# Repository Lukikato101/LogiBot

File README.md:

# LogiBot

**Low-cost Autonomous Mobile Robot (AMR) for Warehouse Automation**

LogiBot is an autonomous mobile robot project focused on building an affordable and practical warehouse automation platform for small and medium-sized warehouses.

The goal of this project is to develop a reliable AMR system that can transport materials, navigate autonomously, and serve as a foundation for future warehouse automation solutions.

---

## Vision

Warehouse automation should not be limited to large enterprises.

LogiBot aims to make autonomous material transport more accessible by developing a cost-effective AMR platform that can be deployed in real-world warehouse environments.

---

## Project Goals

* Build a reliable autonomous mobile robot platform
* Develop a low-cost warehouse transportation solution
* Create a modular hardware and software architecture
* Support ROS 2 based development
* Enable fleet management and multi-robot operations
* Provide a foundation for future commercial deployment

---

## Current Development Status

### Phase 1 — Mobile Robot Platform

* [ ] Differential drive platform
* [ ] STM32 motor controller
* [ ] Encoder integration
* [ ] IMU integration
* [ ] Battery management

### Phase 2 — ROS 2 Integration

* [ ] ROS 2 communication
* [ ] Robot description (URDF)
* [ ] Teleoperation
* [ ] Odometry

### Phase 3 — Autonomous Navigation

* [ ] Localization
* [ ] Waypoint navigation
* [ ] AprilTag navigation
* [ ] Obstacle detection

### Phase 4 — Warehouse Features

* [ ] Material transport workflow
* [ ] Automatic docking
* [ ] Charging station
* [ ] Fleet management dashboard

### Phase 5 — Field Testing

* [ ] Real warehouse deployment
* [ ] Performance optimization
* [ ] Reliability testing

---

## System Architecture

```text
+------------------------+
|      Fleet Manager     |
+-----------+------------+
            |
            v
+------------------------+
|    ROS 2 Computer      |
| (Raspberry Pi / SBC)   |
+-----------+------------+
            |
            v
+------------------------+
|         STM32          |
|  Motor & Sensor Layer  |
+-----------+------------+
            |
            v
+------------------------+
| Motors / Encoders /    |
| IMU / Safety Sensors   |
+------------------------+
```

---

## Repository Structure

```text
LogiBot/

├── docs/
├── hardware/
├── firmware/
├── software/
├── simulation/
├── dashboard/
├── test/
└── README.md
```

### docs/

Project documentation, architecture, roadmap, and technical notes.

### hardware/

Mechanical design, CAD files, PCB designs, and manufacturing resources.

### firmware/

STM32 firmware for motor control, sensors, and communication.

### software/

ROS 2 packages, navigation stack, robot interfaces, and system integration.

### simulation/

Simulation environments and testing tools.

### dashboard/

Fleet monitoring and management interface.

---

## Technology Stack

### Hardware

* STM32
* Differential Drive Platform
* BLDC/DC Motors
* Encoders
* IMU
* Camera
* Battery Management System

### Software

* ROS 2
* Ubuntu
* C++
* Python
* Micro-ROS
* Gazebo

---

## Contribution Areas

There are many ways to contribute:

### Embedded Systems

* STM32 firmware
* Motor control
* Sensor integration
* Communication protocols

### Robotics Software

* ROS 2 packages
* Navigation
* Localization
* Path planning

### Mechanical Design

* Chassis design
* CAD modeling
* Manufacturing optimization

### Electronics

* PCB design
* Power systems
* Safety circuits

### Simulation

* Gazebo environments
* Testing scenarios
* Validation tools

### Documentation

* Tutorials
* Setup guides
* Technical documentation

---

## How to Contribute

1. Fork the repository
2. Create a feature branch
3. Implement your changes
4. Test your work
5. Submit a Pull Request

Please keep contributions focused, documented, and aligned with the project roadmap.

---

## Roadmap

### V0.1

Basic differential drive robot

### V0.2

ROS 2 integration

### V0.3

Autonomous waypoint navigation

### V0.4

Automatic docking

### V0.5

Fleet management

### V1.0

Warehouse-ready AMR platform

---

## Long-Term Objective

Build an affordable warehouse AMR platform that helps small and medium-sized businesses adopt automation without the high costs typically associated with industrial robotics.

---

## Join the Project

If you are interested in robotics, embedded systems, ROS 2, mechanical design, electronics, or warehouse automation, contributions are welcome.

Together we can build a practical and accessible AMR platform from the ground up.

---

**Project Name:** LogiBot

**Status:** Early Development

**License:** To be determined

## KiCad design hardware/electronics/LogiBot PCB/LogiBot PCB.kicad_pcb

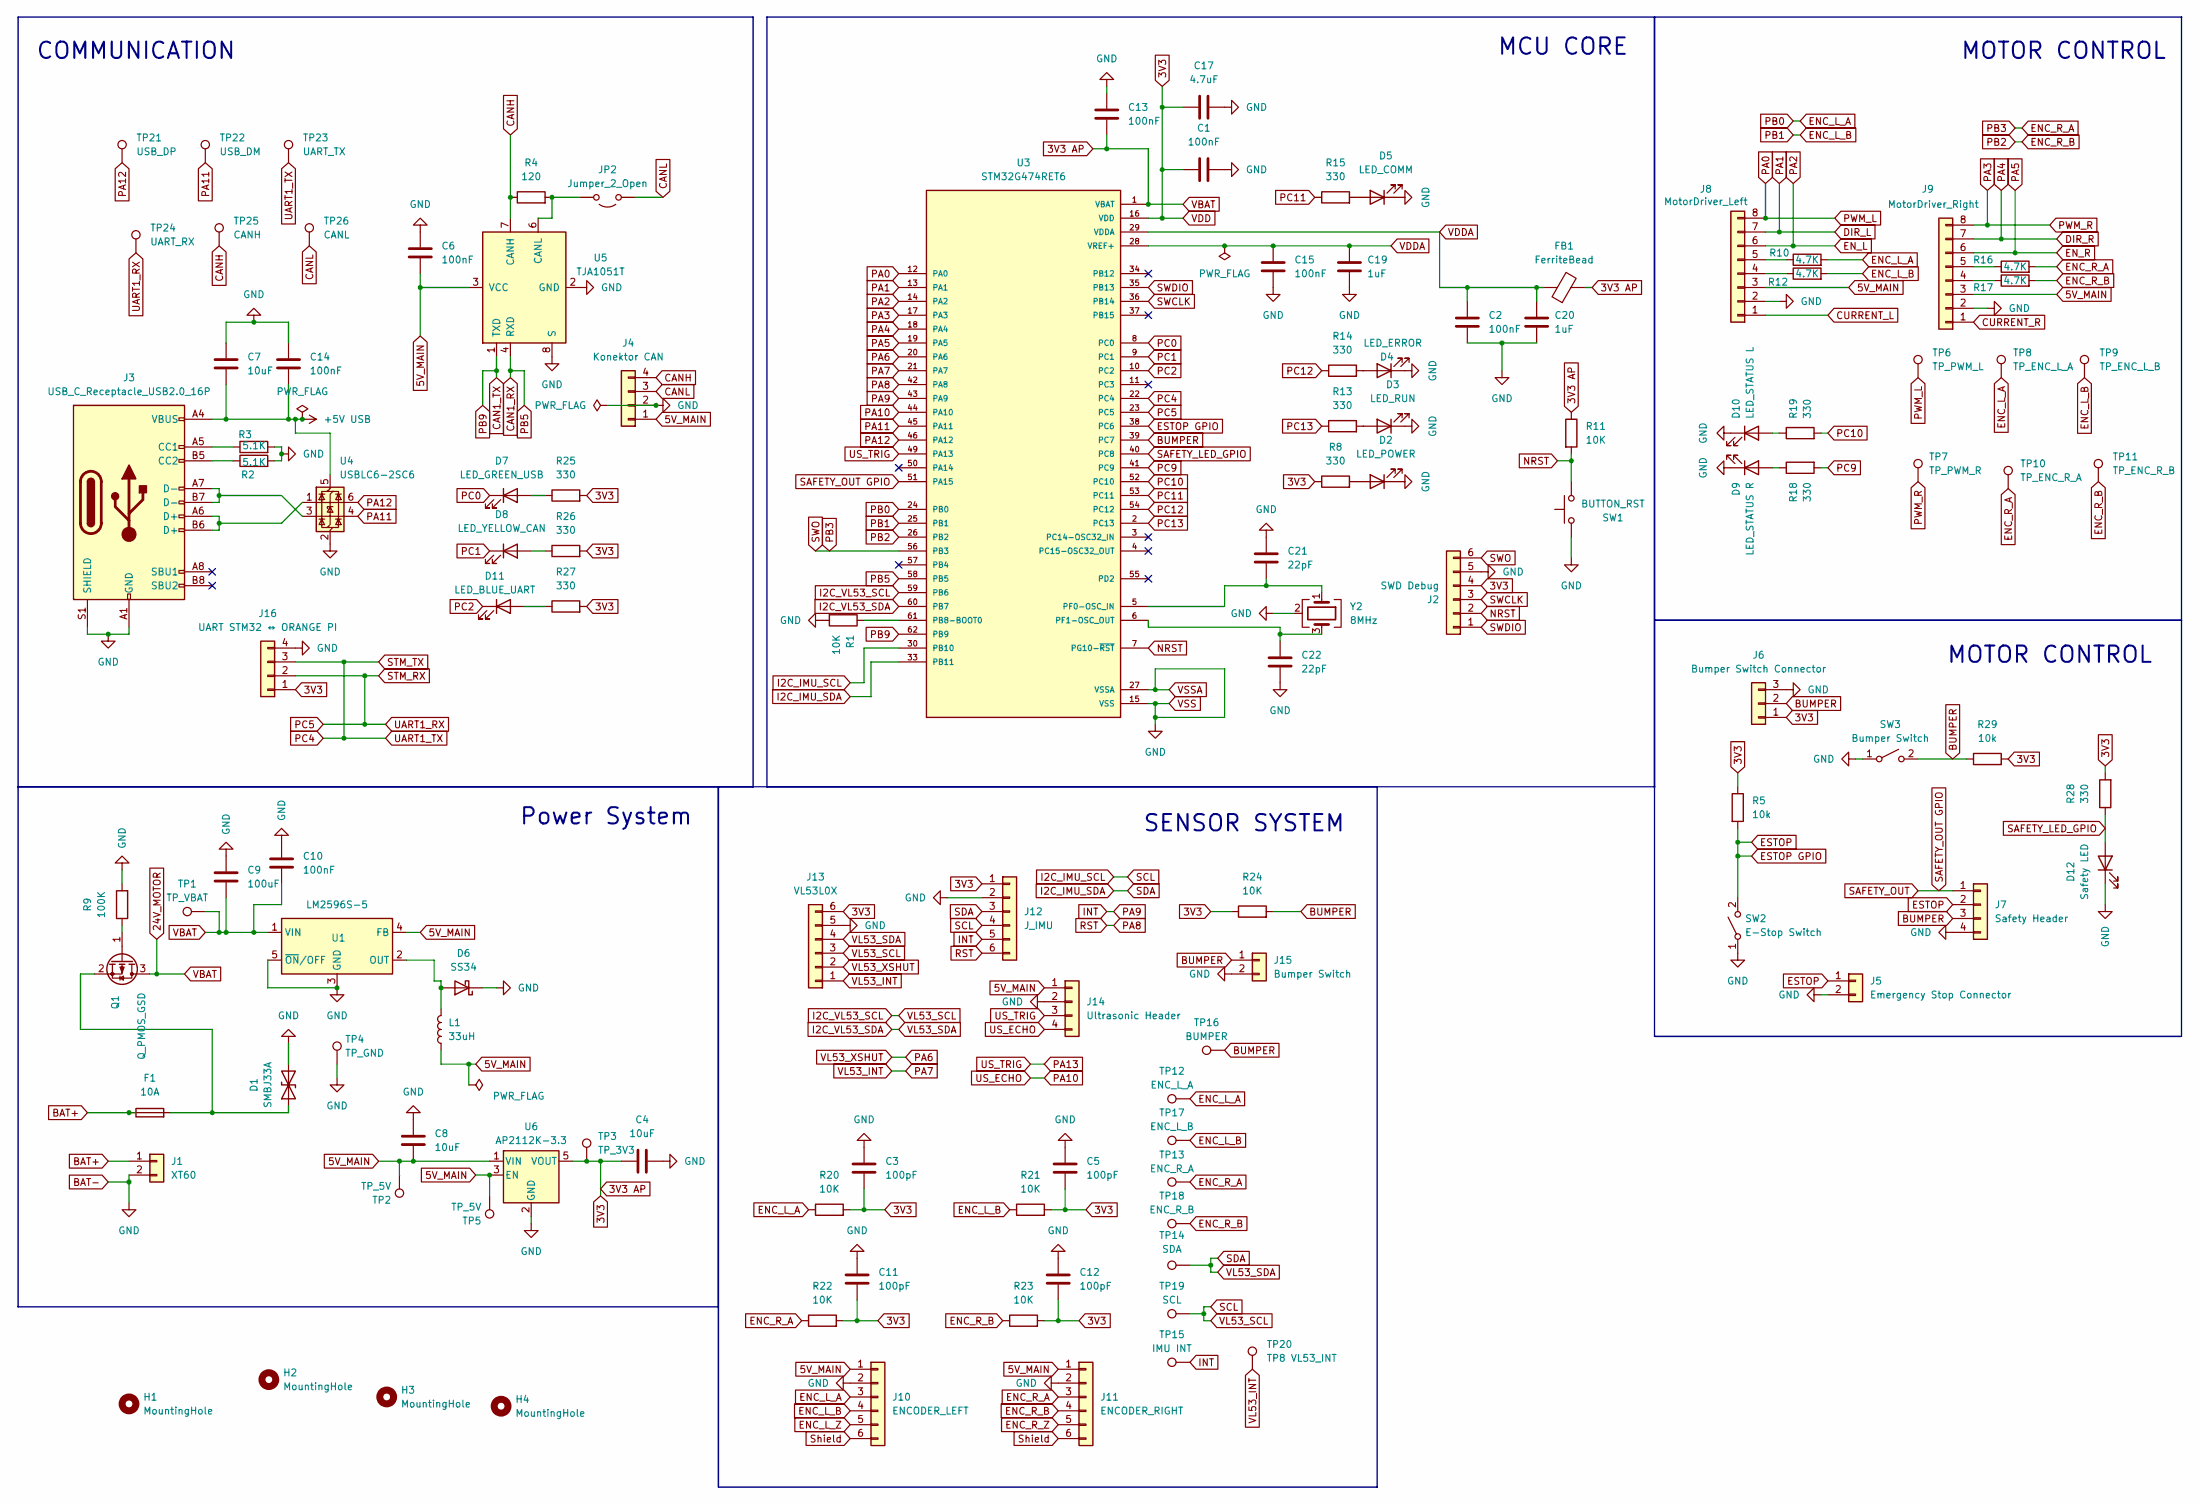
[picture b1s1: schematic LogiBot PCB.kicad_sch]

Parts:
C1, C2, C6, C10, C13, C14, C15: 100nF; C_0603_1608Metric
C3, C5, C11, C12: 100pF; C_0603_1608Metric
C4, C7, C8: 10uF; C_0805_2012Metric
C9: 100uF; CP_Radial_D10.0mm_P5.00mm
C17: 4.7uF; C_0805_2012Metric
C19, C20: 1uF; C_0805_2012Metric
C21, C22: 22pF; C_0603_1608Metric
D1: SMBJ33A; D_SMB
D2: LED_POWER; LED_0805_2012Metric
D3: LED_RUN; LED_0805_2012Metric
D4: LED_ERROR; LED_0805_2012Metric
D5: LED_COMM; LED_0805_2012Metric
D6: SS34; D_SMA
D7: LED_GREEN_USB; LED_0805_2012Metric
D8: LED_YELLOW_CAN; LED_0805_2012Metric
D9: LED_STATUS R; LED_0805_2012Metric
D10: LED_STATUS L; LED_0805_2012Metric
D11: LED_BLUE_UART; LED_0805_2012Metric
D12: Safety LED; LED_0805_2012Metric
F1: 10A; Fuseholder_Blade_Mini_Keystone_3568
FB1: FerriteBead; L_1206_3216Metric
H1, H2, H3, H4: MountingHole; MountingHole_3.2mm_M3
J1: XT60; AMASS_XT60-M_1x02_P7.20mm_Vertical
J2: SWD Debug; PinHeader_1x06_P2.54mm_Vertical
J3: USB_C_Receptacle_USB2.0_16P; USB_C_Receptacle_GCT_USB4105-xx-A_16P_TopMnt_Horizontal
J4: Konektor CAN; JST_XH_B4B-XH-A_1x04_P2.50mm_Vertical
J5: Emergency Stop Connector; JST_XH_B2B-XH-A_1x02_P2.50mm_Vertical
J6: Bumper Switch Connector; JST_XH_B3B-XH-A_1x03_P2.50mm_Vertical
J7: Safety Header; JST_XH_B4B-XH-A_1x04_P2.50mm_Vertical
J8: MotorDriver_Left; JST_XH_B8B-XH-A_1x08_P2.50mm_Vertical
J9: MotorDriver_Right; JST_XH_B8B-XH-A_1x08_P2.50mm_Vertical
J10: ENCODER_LEFT; JST_XH_B6B-XH-A_1x06_P2.50mm_Vertical
J11: ENCODER_RIGHT; JST_XH_B6B-XH-A_1x06_P2.50mm_Vertical
J12: J_IMU; JST_XH_B6B-XH-A_1x06_P2.50mm_Vertical
J13: VL53L0X; JST_XH_B6B-XH-A_1x06_P2.50mm_Vertical
J14: Ultrasonic Header; JST_XH_B4B-XH-A_1x04_P2.50mm_Vertical
J15: Bumper Switch; JST_XH_B2B-XH-A_1x02_P2.50mm_Vertical
J16: UART STM32 ↔ ORANGE PI; JST_XH_B4B-XH-A_1x04_P2.50mm_Vertical
JP2: Jumper_2_Open; SolderJumper-2_P1.3mm_Bridged2Bar_Pad1.0x1.5mm
L1: 33uH; INDP125125X600N
Q1: Q_PMOS_GSD; SOT-23
R1, R11, R20, R21, R22, R23, R24: 10K; R_0603_1608Metric
R2, R3: 5.1K; R_0603_1608Metric
R4: 120; R_0603_1608Metric
R5, R29: 10k; R_0603_1608Metric
R8, R13, R14, R15, R18, R19, R25, R26, R27, R28: 330; R_0603_1608Metric
R9: 100K; R_0603_1608Metric
R10, R12, R16, R17: 4.7K; R_0603_1608Metric
SW1: BUTTON_RST; SW_PUSH_6mm
SW2: E-Stop Switch; TestPoint_Pad_D1.5mm
SW3: Bumper Switch; TestPoint_Pad_D1.5mm
TP1: TP_VBAT; TestPoint_Pad_D1.5mm
TP2, TP5: TP_5V; TestPoint_Pad_D1.5mm
TP3: TP_3V3; TestPoint_Pad_D1.5mm
TP4: TP_GND; TestPoint_Pad_D1.5mm
TP6: TP_PWM_L; TestPoint_Pad_D1.5mm
TP7: TP_PWM_R; TestPoint_Pad_D1.5mm
TP8: TP_ENC_L_A; TestPoint_Pad_D1.5mm
TP9: TP_ENC_L_B; TestPoint_Pad_D1.5mm
TP10: TP_ENC_R_A; TestPoint_Pad_D1.5mm
TP11: TP_ENC_R_B; TestPoint_Pad_D1.5mm
TP12: ENC_L_A; TestPoint_Pad_D1.5mm
TP13: ENC_R_A; TestPoint_Pad_D1.5mm
TP14: SDA; TestPoint_Pad_D1.5mm
TP15: IMU INT; TestPoint_Pad_D1.5mm
TP16: BUMPER; TestPoint_Pad_D1.5mm
TP17: ENC_L_B; TestPoint_Pad_D1.5mm
TP18: ENC_R_B; TestPoint_Pad_D1.5mm
TP19: SCL; TestPoint_Pad_D1.5mm
TP20: TP8 VL53_INT; TestPoint_Pad_D1.5mm
TP21: USB_DP; TestPoint_Pad_D1.5mm
TP22: USB_DM; TestPoint_Pad_D1.5mm
TP23: UART_TX; TestPoint_Pad_D1.5mm
TP24: UART_RX; TestPoint_Pad_D1.5mm
TP25: CANH; TestPoint_Pad_D1.5mm
TP26: CANL; TestPoint_Pad_D1.5mm
U1: LM2596S-5; TO-263-5_TabPin3
U3: STM32G474RET6; QFP50P1200X1200X160-64N; PARTREV 6
U4: USBLC6-2SC6; SOT-23-6
U5: TJA1051T; SOIC-8_3.9x4.9mm_P1.27mm
U6: AP2112K-3.3; SOT-23-5
Y2: 8MHz; Crystal_SMD_3225-4Pin_3.2x2.5mm

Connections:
5V_MAIN: C6.2, C8.2, J4.1, J8.3, J9.3, J10.1, J11.1, J14.1, L1.1, TP2.1 (1_1), TP5.1 (1_1), U1.4 (FB), U5.3 (VCC), U6.1 (VIN), U6.3 (EN); also elsewhere on the board
24V_MOTOR: C1.1, C3.2, C4.2, C5.2, C9.2, C10.2, C11.2, C12.2, C13.2, C17.1, FB1.2, J2.4, J6.1, J12.1, J13.6, J16.1, Q1.3 (D), R5.1, R8.1, R11.1, R20.2, R21.2, R22.2, R23.2, R24.1, R25.2, R26.2, R27.2, R28.2, R29.2, TP1.1 (1_1), TP3.1 (1_1), U1.1 (VIN), U3.1 (VBAT), U3.16 (VDD), U3.32 (VDD), U3.48 (VDD), U3.64 (VDD), U6.5 (VOUT)
+5V USB: C7.2, C14.2, J3.A4 (VBUS), J3.A9 (VBUS), J3.B4 (VBUS), J3.B9 (VBUS), U4.5 (VBUS)
BAT+: F1.1, J1.1
BAT-: C1.2, C2.2, C3.1, C4.1, C5.1, C6.1, C7.1, C8.1, C9.1, C10.1, C11.1, C12.1, C13.1, C14.1, C15.2, C17.2, C19.2, C20.2, C21.1, C22.2, D1.2 (A2), D2.1 (K), D3.1 (K), D4.1 (K), D5.1 (K), D6.1 (K), D9.1 (K), D10.1 (K), D12.1 (K), J1.2, J2.5, J3.A1 (GND), J3.A12 (GND), J3.B1 (GND), J3.B12 (GND), J3.S1 (SHIELD), J4.2, J5.2, J6.3, J7.4, J8.2, J9.2, J10.2, J11.2, J12.2, J13.5, J14.2, J15.2, J16.4, R1.2, R2.2, R3.2, R9.2, SW1.1, SW2.1 (A_1), SW3.1 (A_1), TP4.1 (1_1), U1.3 (GND), U1.5 (~ON/OFF), U3.15 (VSS), U3.27 (VSSA), U3.31 (VSS), U3.47 (VSS), U3.63 (VSS), U4.2 (GND), U5.2 (GND), U5.8 (S), U6.2 (GND), Y2.2 (G), Y2.4 (G); also elsewhere on the board
BUMPER: J6.2, J7.3, J15.1, R24.2, R29.1, SW3.2 (B), TP16.1 (1_1), U3.39 (PC7)
CAN1_RX: U3.58 (PB5), U5.4 (RXD)
CAN1_TX: U3.62 (PB9), U5.1 (TXD)
CANH: J4.4, R4.1, TP25.1 (1_1), U5.7 (CANH)
CANL: J4.3, JP2.1 (A), TP26.1 (1_1)
CURRENT_L: J8.1
CURRENT_R: J9.1; also elsewhere on the board
DIR_L: J8.7, U3.13 (PA1)
DIR_R: J9.7, U3.18 (PA4)
ENC_L_A: J10.3, R10.2, R20.1, TP8.1 (1_1), TP12.1 (1_1), U3.24 (PB0)
ENC_L_B: J10.4, R12.2, R21.1, TP9.1 (1_1), TP17.1 (1_1), U3.25 (PB1)
ENC_L_Z: J10.5
ENC_R_A: J2.6, J11.3, R16.2, R22.1, TP10.1 (1_1), TP13.1 (1_1), U3.56 (PB3)
ENC_R_B: J11.4, R17.2, R23.1, TP11.1 (1_1), TP18.1 (1_1), U3.26 (PB2)
ENC_R_Z: J11.5
EN_L: J8.6, U3.14 (PA2)
EN_R: J9.6, U3.19 (PA5)
ESTOP: J5.1, J7.2, R5.2, SW2.2 (B), U3.38 (PC6)
I2C_IMU_SCL: J12.4, J13.3, TP19.1 (1_1), U3.30 (PB10), U3.59 (PB6)
I2C_IMU_SDA: J12.3, J13.4, TP14.1 (1_1), U3.33 (PB11), U3.60 (PB7)
INT: J12.5, TP15.1 (1_1), U3.43 (PA9)
NRST: J2.2, R11.2, SW1.2, U3.7 (PG10-~RST)
unnamed: D1.1 (A1), F1.2, Q1.2 (S)
unnamed: D2.2 (A), R8.2
unnamed: D3.2 (A), R13.2
unnamed: D4.2 (A), R14.2
unnamed: D5.2 (A), R15.2
unnamed: D6.2 (A), L1.2, U1.2 (OUT)
unnamed: D7.2 (A), R25.1
unnamed: D8.2 (A), R26.1
unnamed: D9.2 (A), R18.1
unnamed: D10.2 (A), R19.1
unnamed: D11.2 (A), R27.1
unnamed: J3.A5 (CC1), R3.1
unnamed: J3.B5 (CC2), R2.1
unnamed: J3.A6 (D+), J3.B6 (D+), U4.1 (I/O1)
unnamed: J3.A7 (D-), J3.B7 (D-), U4.3 (I/O2)
unnamed: J8.4, R12.1
unnamed: J8.5, R10.1
unnamed: J9.4, R17.1
unnamed: J9.5, R16.1
unnamed: JP2.2 (B), R4.2, U5.6 (CANL)
unnamed: Q1.1 (G), R9.1
unnamed: R1.1, U3.61 (PB8-BOOT0)
unnamed: C21.2, U3.5 (PF0-OSC_IN), Y2.1
unnamed: C22.1, U3.6 (PF1-OSC_OUT), Y2.3
PA0: J8.8, TP6.1 (1_1), U3.12 (PA0)
PA3: J9.8, TP7.1 (1_1), U3.17 (PA3)
PA6: J13.2, U3.20 (PA6)
PA7: J13.1, TP20.1 (1_1), U3.21 (PA7)
PA8: J12.6, U3.42 (PA8)
PA10: J14.4, U3.44 (PA10)
PA11: TP22.1 (1_1), U3.45 (PA11), U4.4 (I/O2)
PA12: TP21.1 (1_1), U3.46 (PA12), U4.6 (I/O1)
PA13: J14.3, U3.49 (PA13)
PC0: D7.1 (K), U3.8 (PC0)
PC1: D8.1 (K), U3.9 (PC1)
PC2: D11.1 (K), U3.10 (PC2)
PC4: J16.3, TP23.1 (1_1), U3.22 (PC4)
PC5: J16.2, TP24.1 (1_1), U3.23 (PC5)
PC9: R18.2, U3.41 (PC9)
PC10: R19.2, U3.52 (PC10)
PC11: R15.1, U3.53 (PC11)
PC12: R14.1, U3.54 (PC12)
PC13: R13.1, U3.2 (PC13)
SAFETY_LED_GPIO: D12.2 (A), R28.1, U3.40 (PC8)
SAFETY_OUT: J7.1, U3.51 (PA15)
SWCLK: J2.3, U3.36 (PB14)
SWDIO: J2.1, U3.35 (PB13)
Shield: J10.6, J11.6
VDDA: C2.1, C15.1, C19.1, C20.1, FB1.1, U3.28 (VREF+), U3.29 (VDDA)

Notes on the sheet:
COMMUNICATION
MOTOR CONTROL
SENSOR SYSTEM
MOTOR CONTROL
MCU CORE
Power System

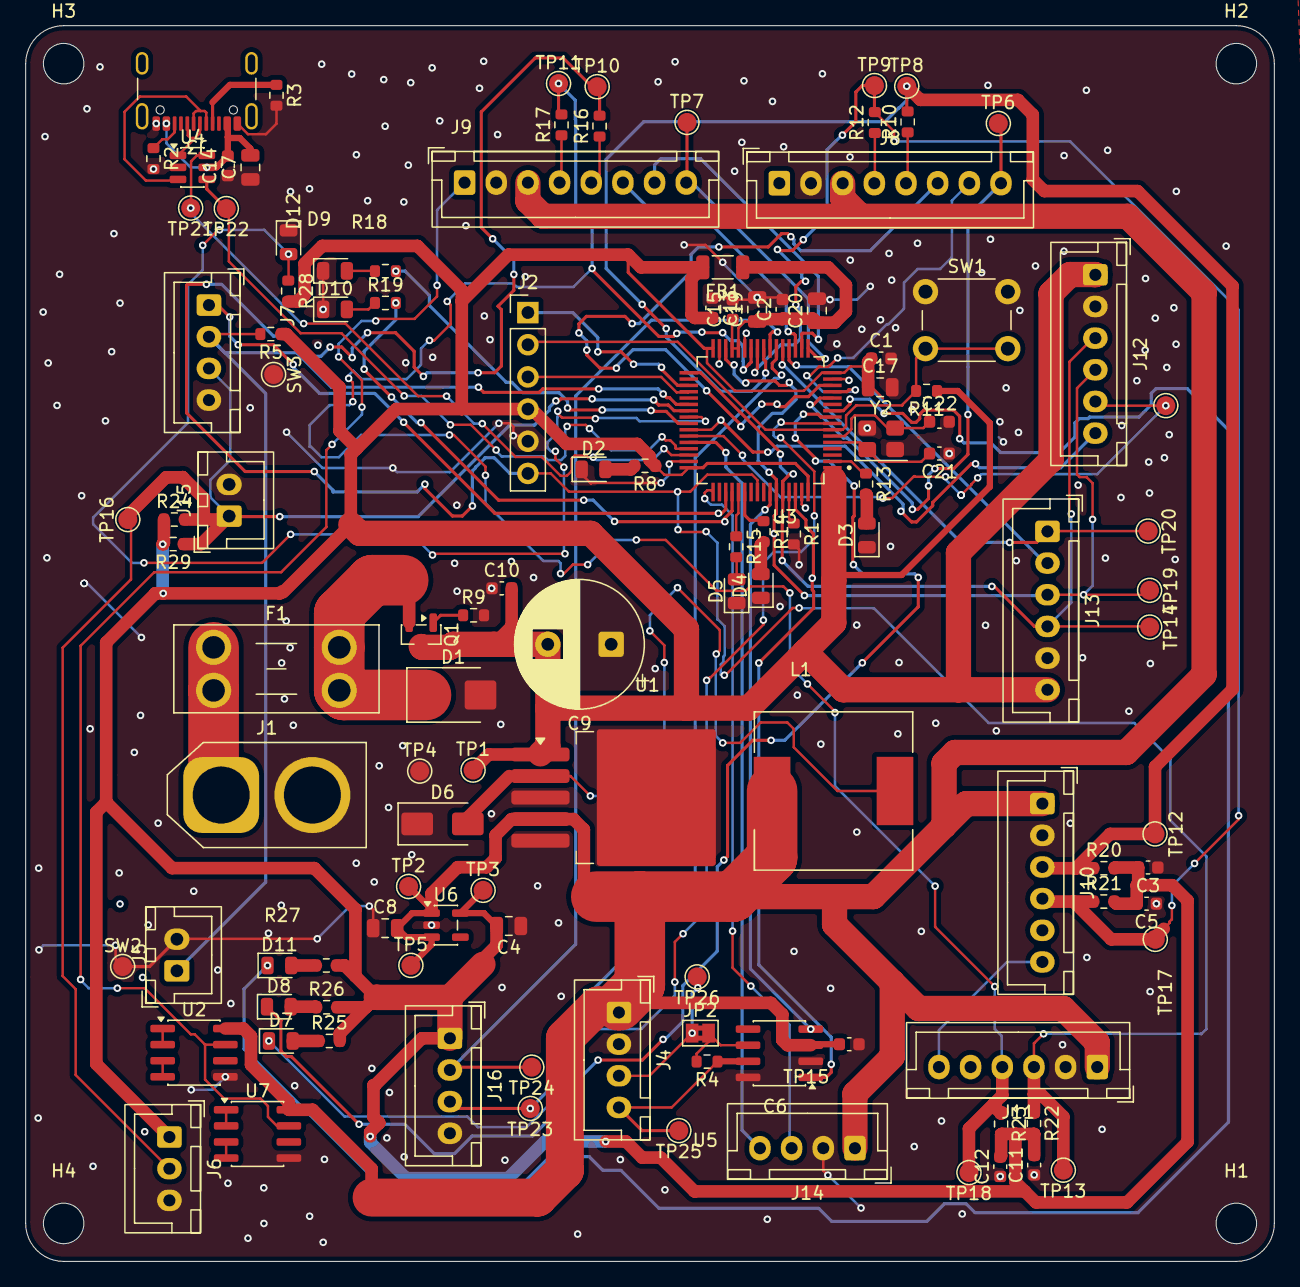
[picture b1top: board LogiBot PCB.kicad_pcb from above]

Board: 4 copper layers, 98.6 x 97.6 mm, 121 parts (0 on the bottom side), 77 nets.

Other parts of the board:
U2: ACS712xLCTR-20A_MRIGHT; SOIC-8_3.9x4.9mm_P1.27mm
U7: ACS712xLCTR-20A_MLEFT; SOIC-8_3.9x4.9mm_P1.27mm

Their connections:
5V_MAIN: U2.8 (VCC), U7.8 (VCC); also elsewhere on the board
BAT-: U2.5 (GND), U7.5 (GND); also elsewhere on the board
CURRENT_R: U2.7 (VIOUT), U7.7 (VIOUT); also elsewhere on the board
unnamed: U2.1 (IP+), U2.2 (IP+)
unnamed: U2.3 (IP-), U2.4 (IP-)
unnamed: U7.1 (IP+), U7.2 (IP+)
unnamed: U7.3 (IP-), U7.4 (IP-)
